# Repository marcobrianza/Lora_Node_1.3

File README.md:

# LoRa Node 1.3
PCB design by Mauro Alfieri and Marco Brianza

A LoRa shield for [WeMos](https://www.wemos.cc/) D1 mini boards  
Made to experiment a LoRaWan radio node and single channel gateway.
based on the projects:  

* WeMos-Lora [https://github.com/hallard/WeMos-Lora](https://github.com/hallard/WeMos-Lora)
* Wemos shield template [https://github.com/SuperHouse/D1MSHO](https://github.com/SuperHouse/D1MSHO)

PCB tested ready for manufactoring:  

* PCBWay [https://www.pcbway.com/project/shareproject/LoRa_Node_1_3.html](https://www.pcbway.com/project/shareproject/LoRa_Node_1_3.html)  
* PCBs.io [https://PCBs.io/share/4XRGg](https://PCBs.io/share/4XRGg) 

The reference BOM:  
[http://www.tme.eu/parking/d9c2f42be567335629e84ae2b3406e02d69110b7.html
](http://www.tme.eu/parking/d9c2f42be567335629e84ae2b3406e02d69110b7.html)

To use the board as node use this version of the lmic LoRa library:  
[https://github.com/marcobrianza/arduino-lmic](https://github.com/marcobrianza/arduino-lmic)  
It supports the LoraNode 1.3 pinout and fixes the radio power setting

Some practial examples with wrapping of the LMIC in more Arduinistic way are here:
[https://github.com/marcobrianza/LoraNode_Examples](https://github.com/marcobrianza/LoraNode_Examples)

To use it as gateway this repo:  
[https://github.com/marcobrianza/ESP-1ch-Gateway-v4.0/tree/LoraNode_1.3](https://github.com/marcobrianza/ESP-1ch-Gateway-v4.0/tree/LoraNode_1.3) 

## Usage Notes
The pinout is as the following table  

* I2C pins are free to be used for sensors or GPIO (pull up resistor are optional on the bottom) 
* D0 is free and can be connected to Reset with the "sleep" pad on the bottom of the board 
* The 2 switches (normally opened) are shared with the serial port pins
* The LED is connecred in parallel with the Built in LED of Wemos 

## Pictures

The board assembled top and bottom

The board in use as node and gateway with wemos oled display

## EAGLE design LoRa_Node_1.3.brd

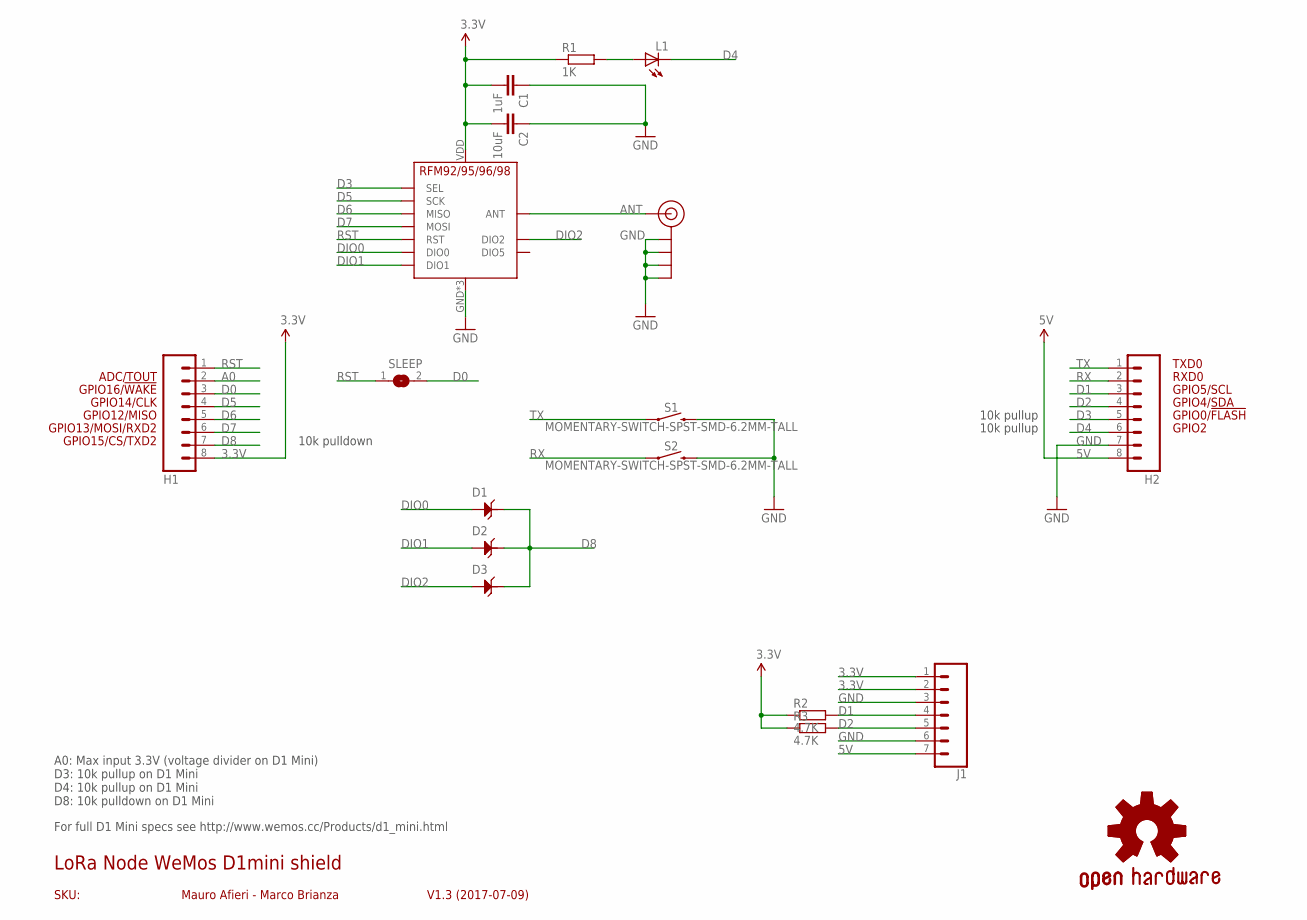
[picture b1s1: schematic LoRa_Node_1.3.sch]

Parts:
C1: 1uF; 0805-CAP-LARGEPADS
C2: 10uF; 0805-CAP-LARGEPADS
D1, D2, D3: D-ESD-2P-CESD5V0D1; SOD123-2.7X1.6
GOLD_ORB_SM1: OSHWLOGO_GOLD_ORB_SM; OSHW2
H1, H2: M08; 1X08
J1: CONN_07; 1X07
J$1: ANTENNATINY; SMA_UFL_PAD_TINY
L1: LEDCHIPLED_0805; CHIPLED_0805
R1: 1K; M0805
R2, R3: 4.7K; M0805
S1, S2: MOMENTARY-SWITCH-SPST-SMD-6.2MM-TALL; TACTILE_SWITCH_SMD_6.2MM_TALL
SLEEP: SJ
U$2: RFM95

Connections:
3.3V: C1.2, C2.2, H1.8, J1.1, J1.2, R1.1, R2.1, R3.1, U$2.VDD (VCC)
5V: H2.8, J1.7
A0: H1.2
ANT: J$1.ANT1 (SIGNAL), J$1.ANT2 (SIGNAL), J$1.ANT3 (SIGNAL), U$2.ANT
D0: H1.3, SLEEP.2
D1: H2.3, J1.4, R2.2
D2: H2.4, J1.5, R3.2
D3: H2.5, U$2.NSS (SEL)
D4: H2.6, L1.C
D5: H1.4, U$2.SCK
D6: H1.5, U$2.MISO
D7: H1.6, U$2.MOSI
D8: D1.2, D2.2, D3.2, H1.7
DIO0: D1.1, U$2.DIO0
DIO1: D2.1, U$2.DIO1
DIO2: D3.1, U$2.DIO2
GND: C1.1, C2.1, H2.7, J1.3, J1.6, J$1.GND1 (GND), J$1.GND2 (GND), J$1.GND3 (GND), J$1.GND4 (GND), S1.B2 (2), S2.B2 (2), U$2.GND, U$2.GND1 (GND), U$2.GND2 (GND)
unnamed: L1.A, R1.2
RST: H1.1, SLEEP.1, U$2.RST
RX: H2.2, S2.A2 (1)
TX: H2.1, S1.A2 (1)

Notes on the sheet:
GPIO2
GPIO0/!FLASH
GPIO12/MISO
GPIO4/SDA
GPIO5/SCL
RXD0
TXD0
GPIO13/MOSI/RXD2
GPIO14/CLK
GPIO15/CS/TXD2
GPIO16/!WAKE
SKU:
LoRa Node WeMos D1mini shield
V1.3 (2017-07-09)
Mauro Afieri - Marco Brianza
ADC/TOUT
A0: Max input 3.3V (voltage divider on D1 Mini) D3: 10k pullup on D1 Mini D4: 10k pullup on D1 Mini D8: 10k pulldown on D1 Mini
10k pulldown
10k pullup
For full D1 Mini specs see http://www.wemos.cc/Products/d1_mini.html

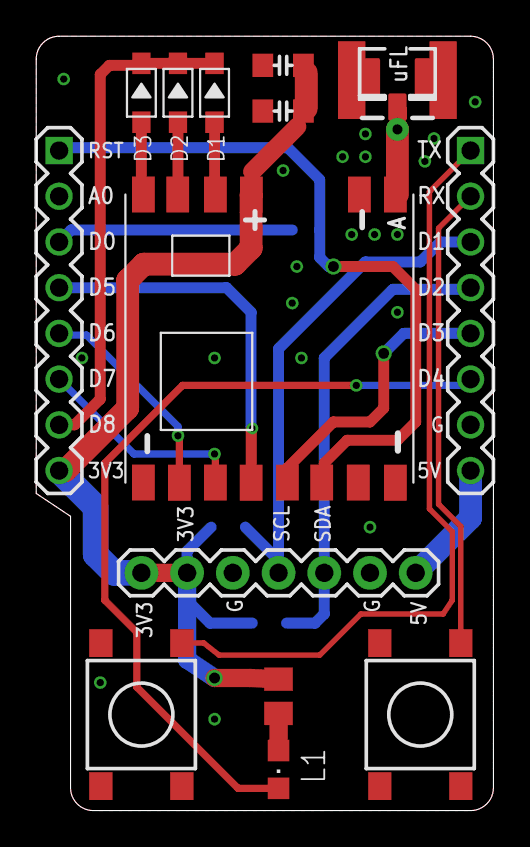
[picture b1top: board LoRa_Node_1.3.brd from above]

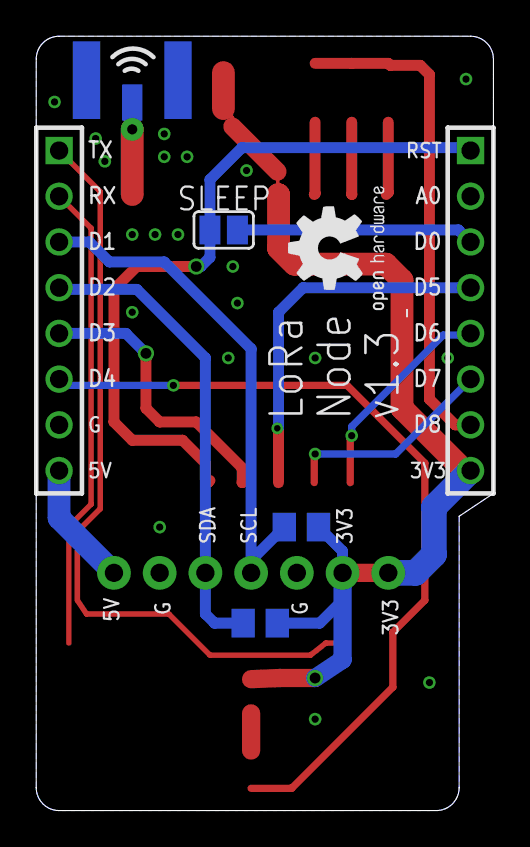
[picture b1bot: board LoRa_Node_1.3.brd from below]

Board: 2 copper layers, 25.4 x 43.0 mm, 18 parts (4 on the bottom side), 20 nets.

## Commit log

2017-07-24 readme additions
2017-08-19 certified as gateway and link to examples
2017-09-21 updated readme and images
2017-09-21 fixed links
2017-09-21 links...

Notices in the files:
parts and their libraries:
freetronics-original: Licensing: CC v3.0 Share-Alike You are welcome to use this library for commercial purposes.
SparkFun-Switches: Licensing: Creative Commons ShareAlike 4.0 International - https://creativecommons.org/licenses/by-sa/4.0
